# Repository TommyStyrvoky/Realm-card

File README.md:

# Realm-card
A compact ESP32 TFT display/lipo charge circuit prop that loops through animations stored in folders on µSD card attached to PCB. Estimated battery life is ~2 hours. 

The length of the animations are limited by the resolution, as the maximum number of frames is limited by RAM space.
The animations are stored in directories under the root of the SD card, these folders are read from and 24 bit bmp images starting from and index of 1 to the maximum number of frames availible or maximum memory will be stored.

The addition of -L to the end of a directory name will make it loop without a randomized delay after completion of the animation.

See Adafruit BOM for additional components needed for the electronics aside from PCB, these were purchased through Adafruit's store, Digi-Key, and Mouser Electronics.
The ESP32 QT-PY will need to be soldered flush onto pads on the PCB, the throughholes are provided for alighment, this should be mounted flush, see assembly directory for photos. Polyamide (Kapton) tape will be used in some areas to insulate the PCB's connections on the back side, for this purpose 0.25" tape was used this is not listed on the BOM. Also not included in the BOM is some strong double sided tape, reccomend a thinner tape for adhesion of the pcb and LCD to the printed parts for removal in the future if needed to change the battery.

A couple revisions were made to the board than the photos that are attached, this removed some redundant components.

Included are KiCAD files for the PCB, there is a custom footprint that was created for the Adafruit QT-PY included. A step and STL file are included for the enclosure.

All production files are set up for manufacture using JLC PCB's service. BOM's and placement files are provided, missing parts may need to be substituted due to component shortages, CAD files and STL files included for printing using their SLA printers in their 8000 resin. Sanding was done after recieving the parts with some priming and sanding to reduce layer lines.
https://jlcpcb.com/

See Adafruit's ESP32 guide on setting up IDE for code upload to microcontroller.
https://learn.adafruit.com/adafruit-qt-py-esp32-pico

Adafruit libraries were used aside from the SPI library.

The enclosure was painted with Vallejo model air metallic, Mr surfacer, and Tamya paints using an airbrush and via a brush.

Primer:

mr surfacer 1000

Tamiya:

XF-1 

X-12 

panel line accent color black

Vallejo

71.062 Aluminum

71.072 Gunmetal

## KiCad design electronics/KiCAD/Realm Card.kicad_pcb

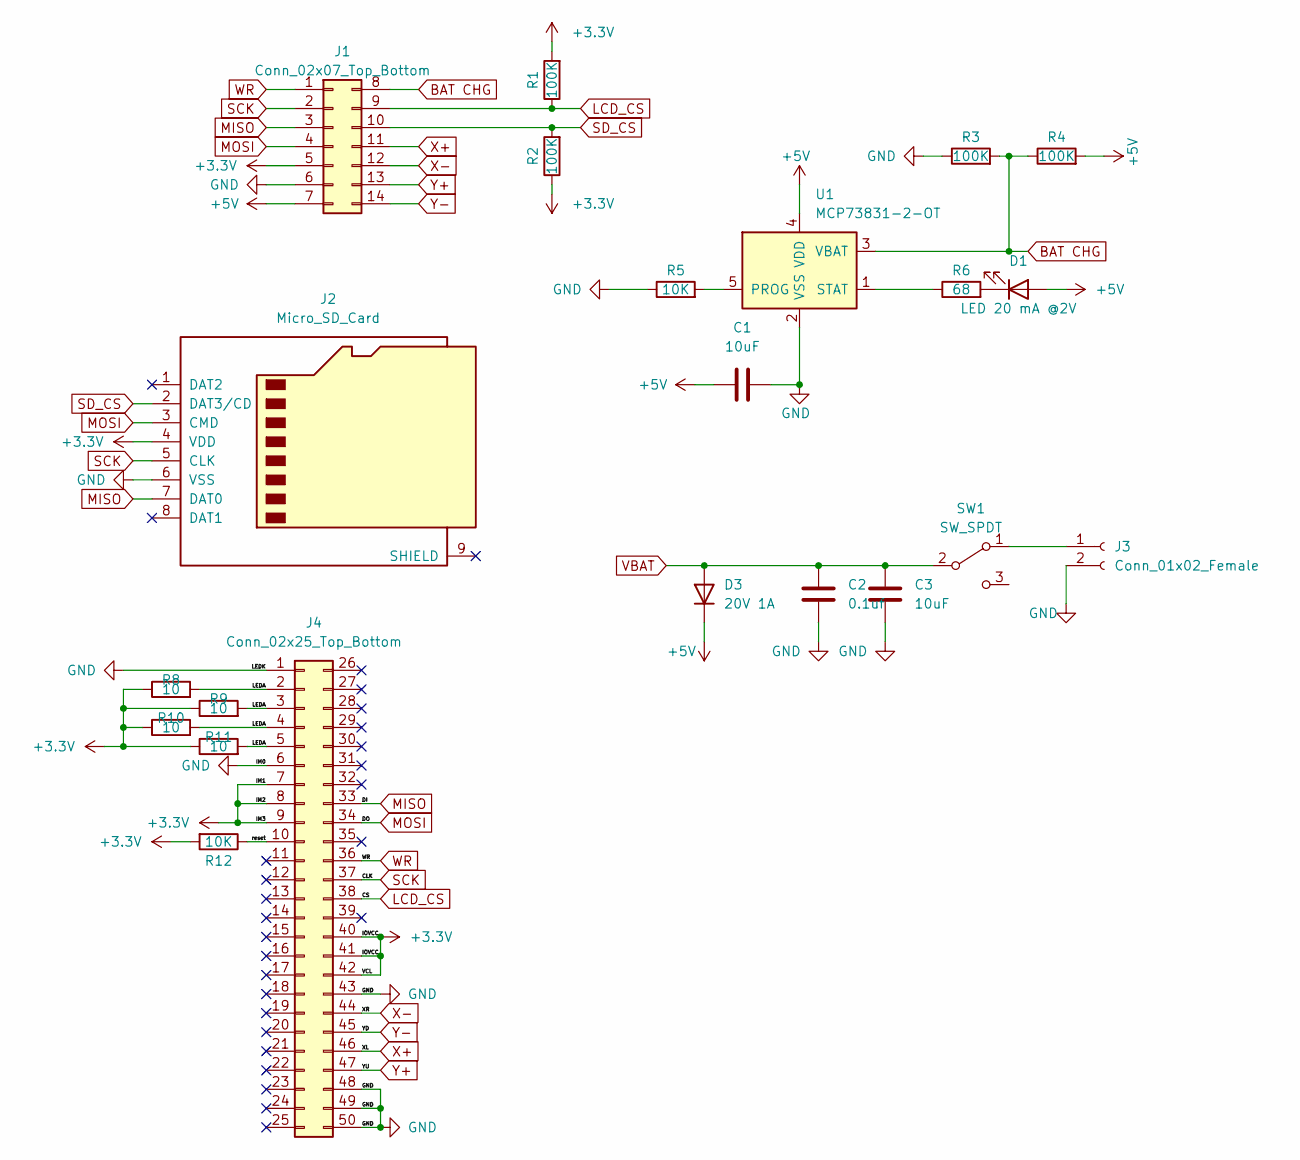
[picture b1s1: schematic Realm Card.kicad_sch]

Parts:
C1, C3: 10uF; C_0805_2012Metric
C2: 0.1uf; C_0805_2012Metric
D1: LED 20 mA @2V; LED_0805_2012Metric; LCSC C2296
D3: 20V 1A; D_SOD-123; LCSC C236132
J1: Conn_02x07_Top_Bottom; Adafruit QT PY
J2: Micro_SD_Card; microSD_HC_Molex_104031-0811; LCSC C585350
J3: Conn_01x02_Female; JST_PH_S2B-PH-SM4-TB_1x02-1MP_P2.00mm_Horizontal; LCSC C295747
J4: Conn_02x25_Top_Bottom; Hirose_FH12-50S-0.5SH_1x50-1MP_P0.50mm_Horizontal; LCSC C375909
R1, R2, R3, R4: 100K; R_0805_2012Metric
R5, R12: 10K; R_0805_2012Metric
R6: 68; R_0805_2012Metric
R8, R9, R10, R11: 10; R_0805_2012Metric
SW1: SW_SPDT; SW_SPDT_CK-JS102011SAQN; LCSC C221660
U1: MCP73831-2-OT; SOT-23-5; LCSC C424093

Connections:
+3.3V: J1.5, J2.4 (VDD), J4.7, J4.8, J4.9, J4.40, J4.41, J4.42, R1.2, R2.1, R8.1, R9.1, R10.1, R11.1, R12.2
+5V: C1.2, D1.2 (A), D3.1 (K), J1.7, R4.2, U1.4 (VDD)
/LEDA: J4.2, J4.3, J4.4, J4.5, R8.2, R9.2, R10.2, R11.2
/reset: J4.10, R12.1
BAT CHG: J1.8, R3.2, R4.1, U1.3 (VBAT)
GND: C1.1, C2.1, C3.1, J1.6, J2.6 (VSS), J3.2, J4.1, J4.6, J4.43, J4.48, J4.49, J4.50, R3.1, R5.1, U1.2 (VSS)
LCD_CS: J1.9, J4.38, R1.1
MISO: J1.3, J2.7 (DAT0), J4.33
MOSI: J1.4, J2.3 (CMD), J4.34
unnamed: D1.1 (K), R6.2
unnamed: J3.1, SW1.1 (A)
unnamed: R5.2, U1.5 (PROG)
unnamed: R6.1, U1.1 (STAT)
SCK: J1.2, J2.5 (CLK), J4.37
SD_CS: J1.10, J2.2 (DAT3/CD), R2.2
VBAT: C2.2, C3.2, D3.2 (A), SW1.2 (B)
WR: J1.1, J4.36
X+: J1.11, J4.46
X-: J1.12, J4.44
Y+: J1.13, J4.47
Y-: J1.14, J4.45

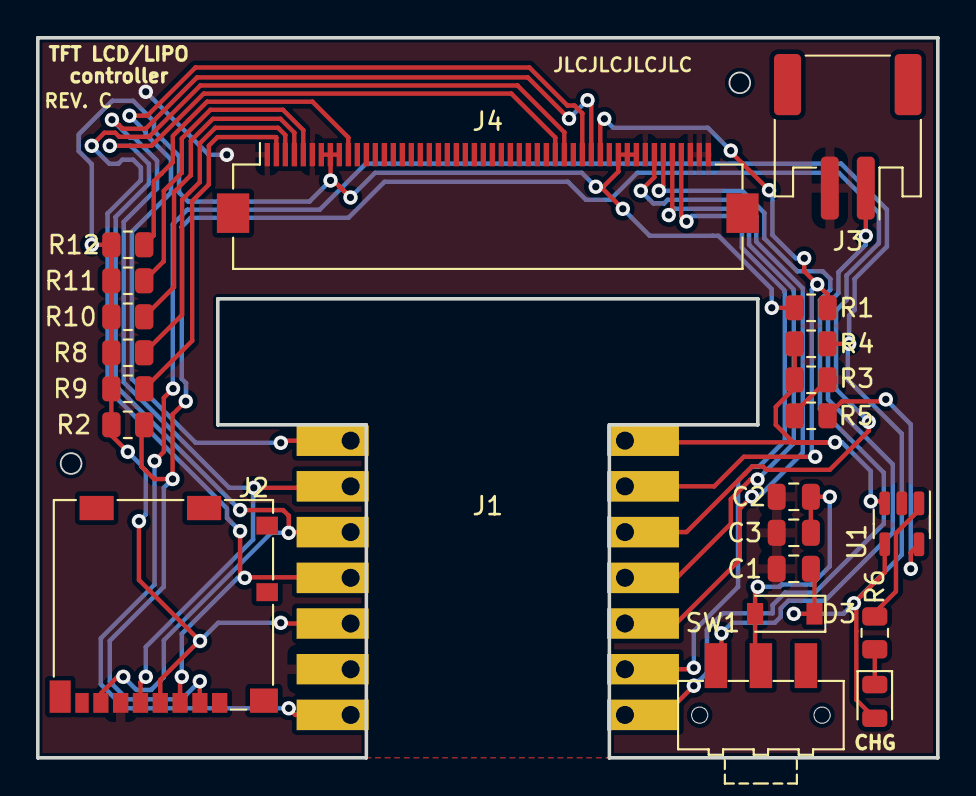
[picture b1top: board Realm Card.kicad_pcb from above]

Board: 2 copper layers, 50.0 x 40.0 mm, 22 parts (0 on the bottom side), 21 nets.

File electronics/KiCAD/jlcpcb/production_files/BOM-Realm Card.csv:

Comment,Designator,Footprint,LCSC
SW_SPDT,SW1,SW_SPDT_CK-JS102011SAQN,C221660
LED 20 mA @2V,D1,LED_0805_2012Metric,C2296
20V 1A,D3,D_SOD-123,C236132
Conn_01x02_Female,J3,JST_PH_S2B-PH-SM4-TB_1x02-1MP_P2.00mm_Horizontal,C295747
Conn_02x25_Top_Bottom,J4,Hirose_FH12-50S-0.5SH_1x50-1MP_P0.50mm_Horizontal,C375909
MCP73831-2-OT,U1,SOT-23-5,C424093
Micro_SD_Card,J2,microSD_HC_Molex_104031-0811,C585350
100K,R3,R_0805_2012Metric,
100K,R1,R_0805_2012Metric,
10,R9,R_0805_2012Metric,
10uF,C1,C_0805_2012Metric,
10,R10,R_0805_2012Metric,
10,R8,R_0805_2012Metric,
10K,R5,R_0805_2012Metric,
Conn_02x07_Top_Bottom,J1,Adafruit QT PY,
100K,R2,R_0805_2012Metric,
0.1uf,C2,C_0805_2012Metric,
68,R6,R_0805_2012Metric,
100K,R4,R_0805_2012Metric,
10,R11,R_0805_2012Metric,
10K,R12,R_0805_2012Metric,
10uF,C3,C_0805_2012Metric,

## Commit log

2022-12-14 Committed files
2022-12-14 Added BOM
2022-12-14 Moved BOM
2022-12-15 revised
2022-12-20 updated board
2022-12-21 revised code
2022-12-28 reworked code
2022-12-30 Added documentation
2022-12-30 revised schematic
